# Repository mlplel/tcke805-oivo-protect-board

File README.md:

# tcke805-oivo-protect-board

KiCad schematic and PC board layout for an add-on over voltage protection circuit for the OIVO Dual DualSense charging cradle.

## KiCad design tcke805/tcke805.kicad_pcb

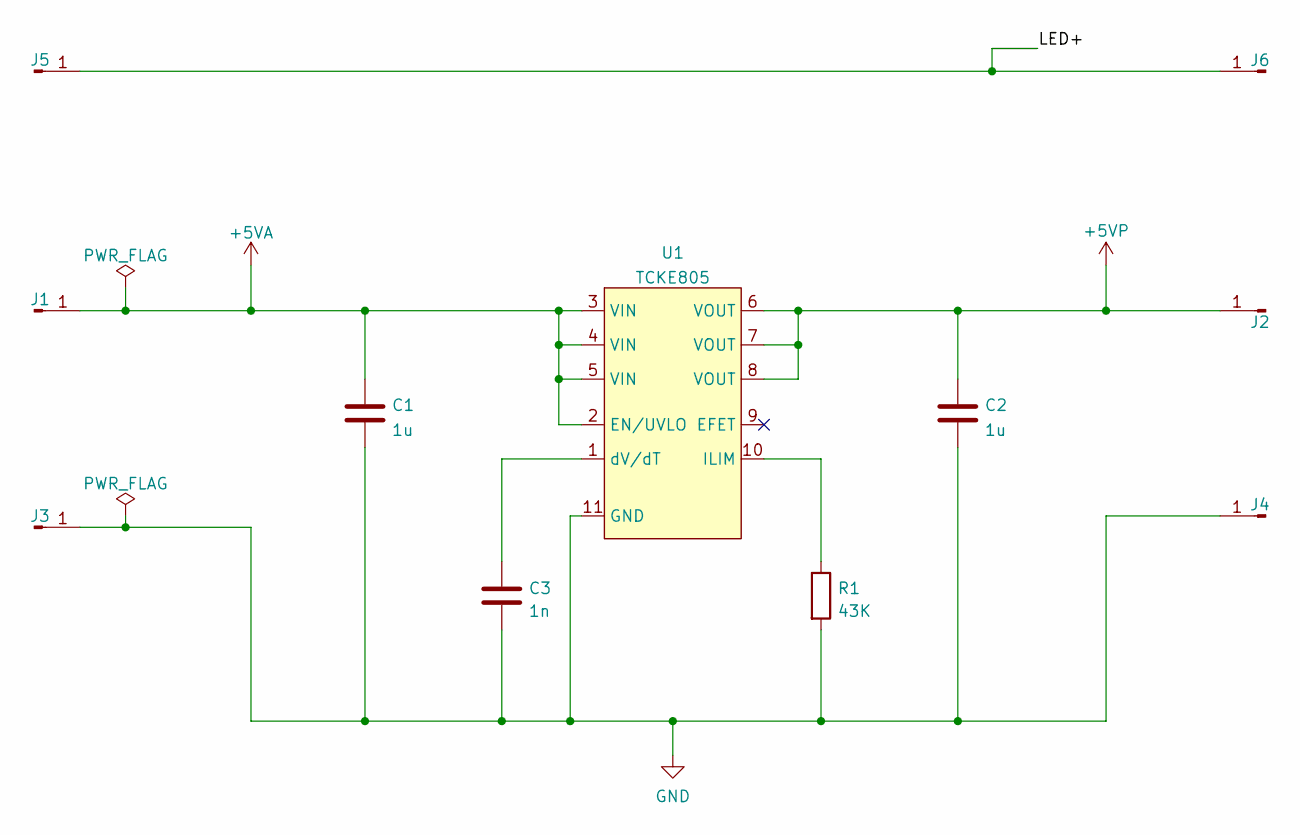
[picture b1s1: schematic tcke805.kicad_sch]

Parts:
C1, C2: 1u; C_0603_1608Metric
C3: 1n; C_0603_1608Metric
J1, J2, J3, J4, J5, J6: Conn_01x01_Male; 1pin_oval
R1: 43K; R_0805_2012Metric
U1: TCKE805; WSON10B

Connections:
+5VA: C1.1, J1.1, U1.2 (EN/UVLO), U1.3 (VIN), U1.4 (VIN), U1.5 (VIN)
+5VP: C2.1, J2.1, U1.6 (VOUT), U1.7 (VOUT), U1.8 (VOUT)
/LED+: J5.1, J6.1
GND: C1.2, C2.2, C3.2, J3.1, J4.1, R1.2, U1.11 (GND)
unnamed: C3.1, U1.1 (dV/dT)
unnamed: R1.1, U1.10 (ILIM)

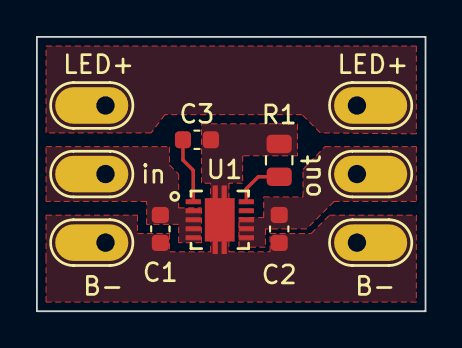
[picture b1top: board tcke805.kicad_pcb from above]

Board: 2 copper layers, 21.6 x 15.2 mm, 11 parts (0 on the bottom side), 6 nets.

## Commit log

2022-08-17 Initial files
